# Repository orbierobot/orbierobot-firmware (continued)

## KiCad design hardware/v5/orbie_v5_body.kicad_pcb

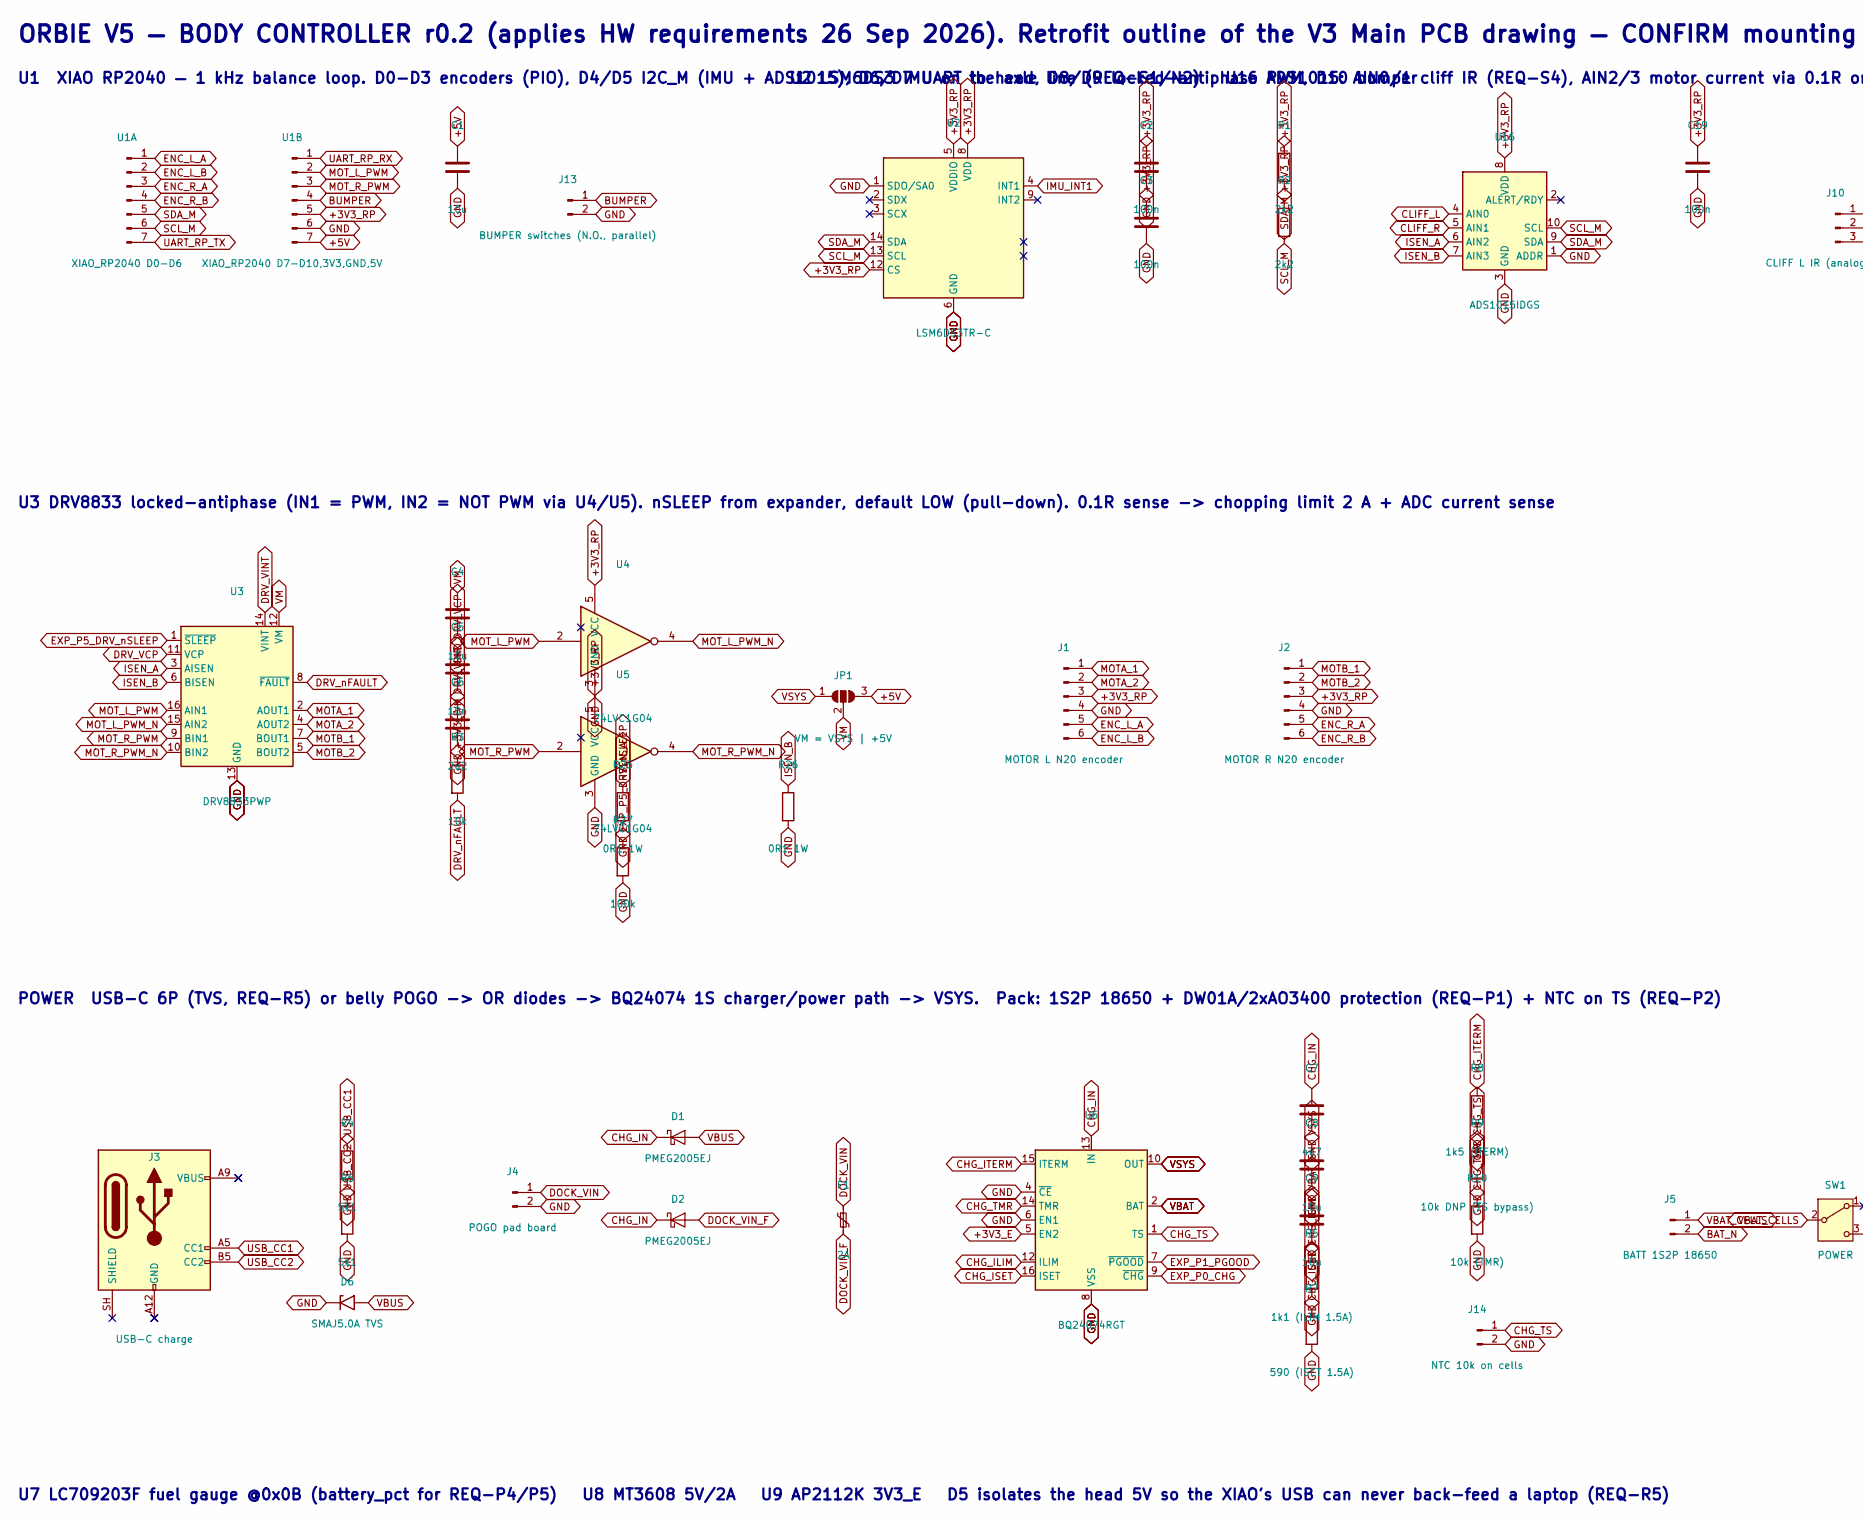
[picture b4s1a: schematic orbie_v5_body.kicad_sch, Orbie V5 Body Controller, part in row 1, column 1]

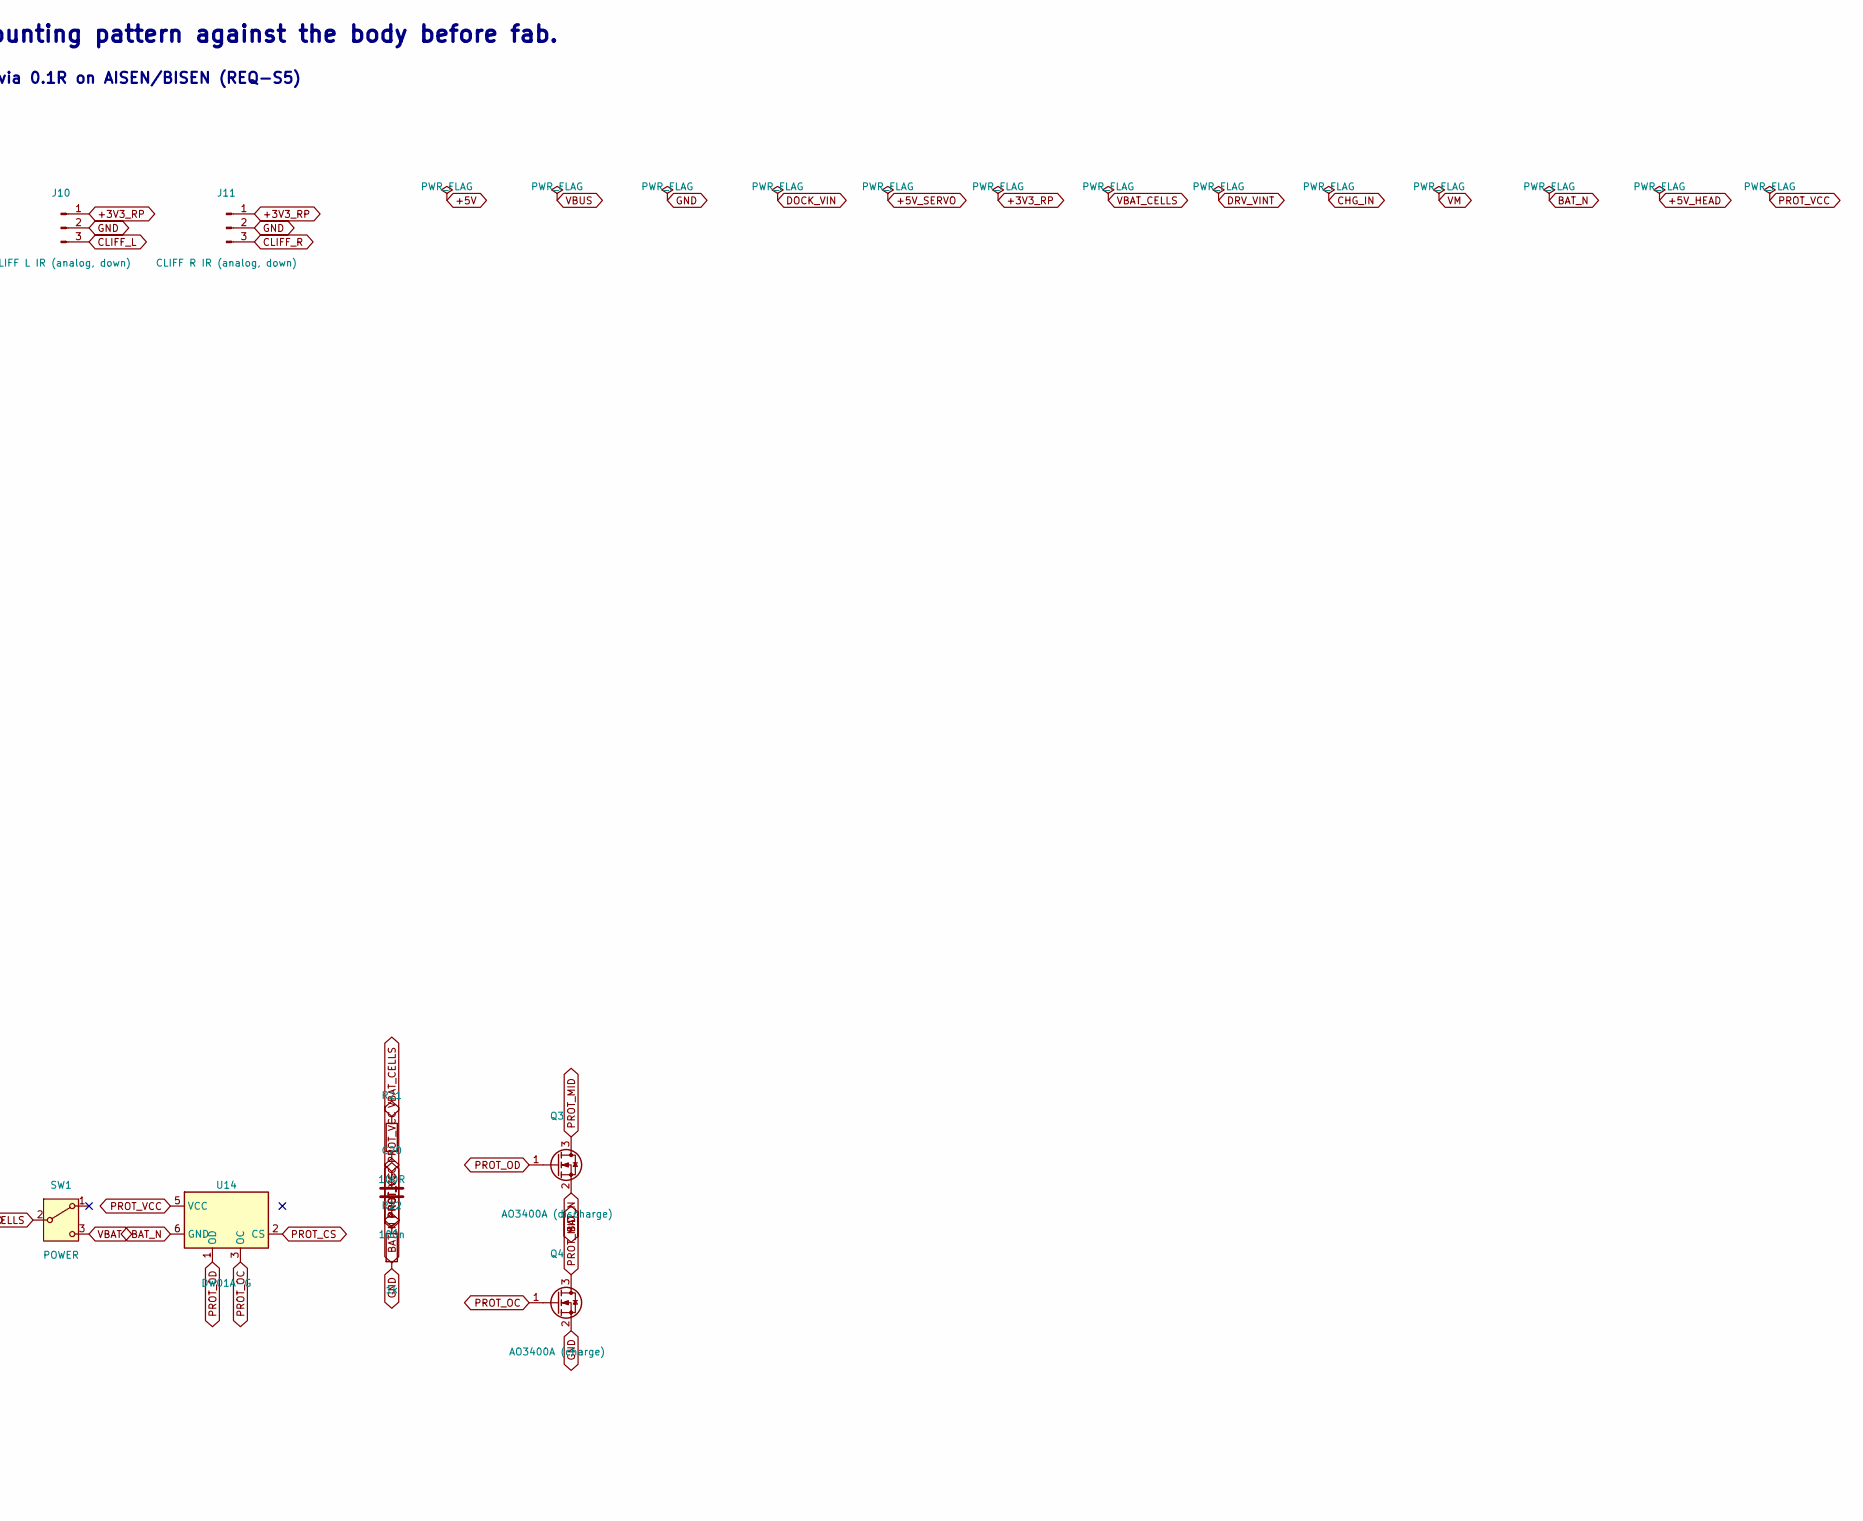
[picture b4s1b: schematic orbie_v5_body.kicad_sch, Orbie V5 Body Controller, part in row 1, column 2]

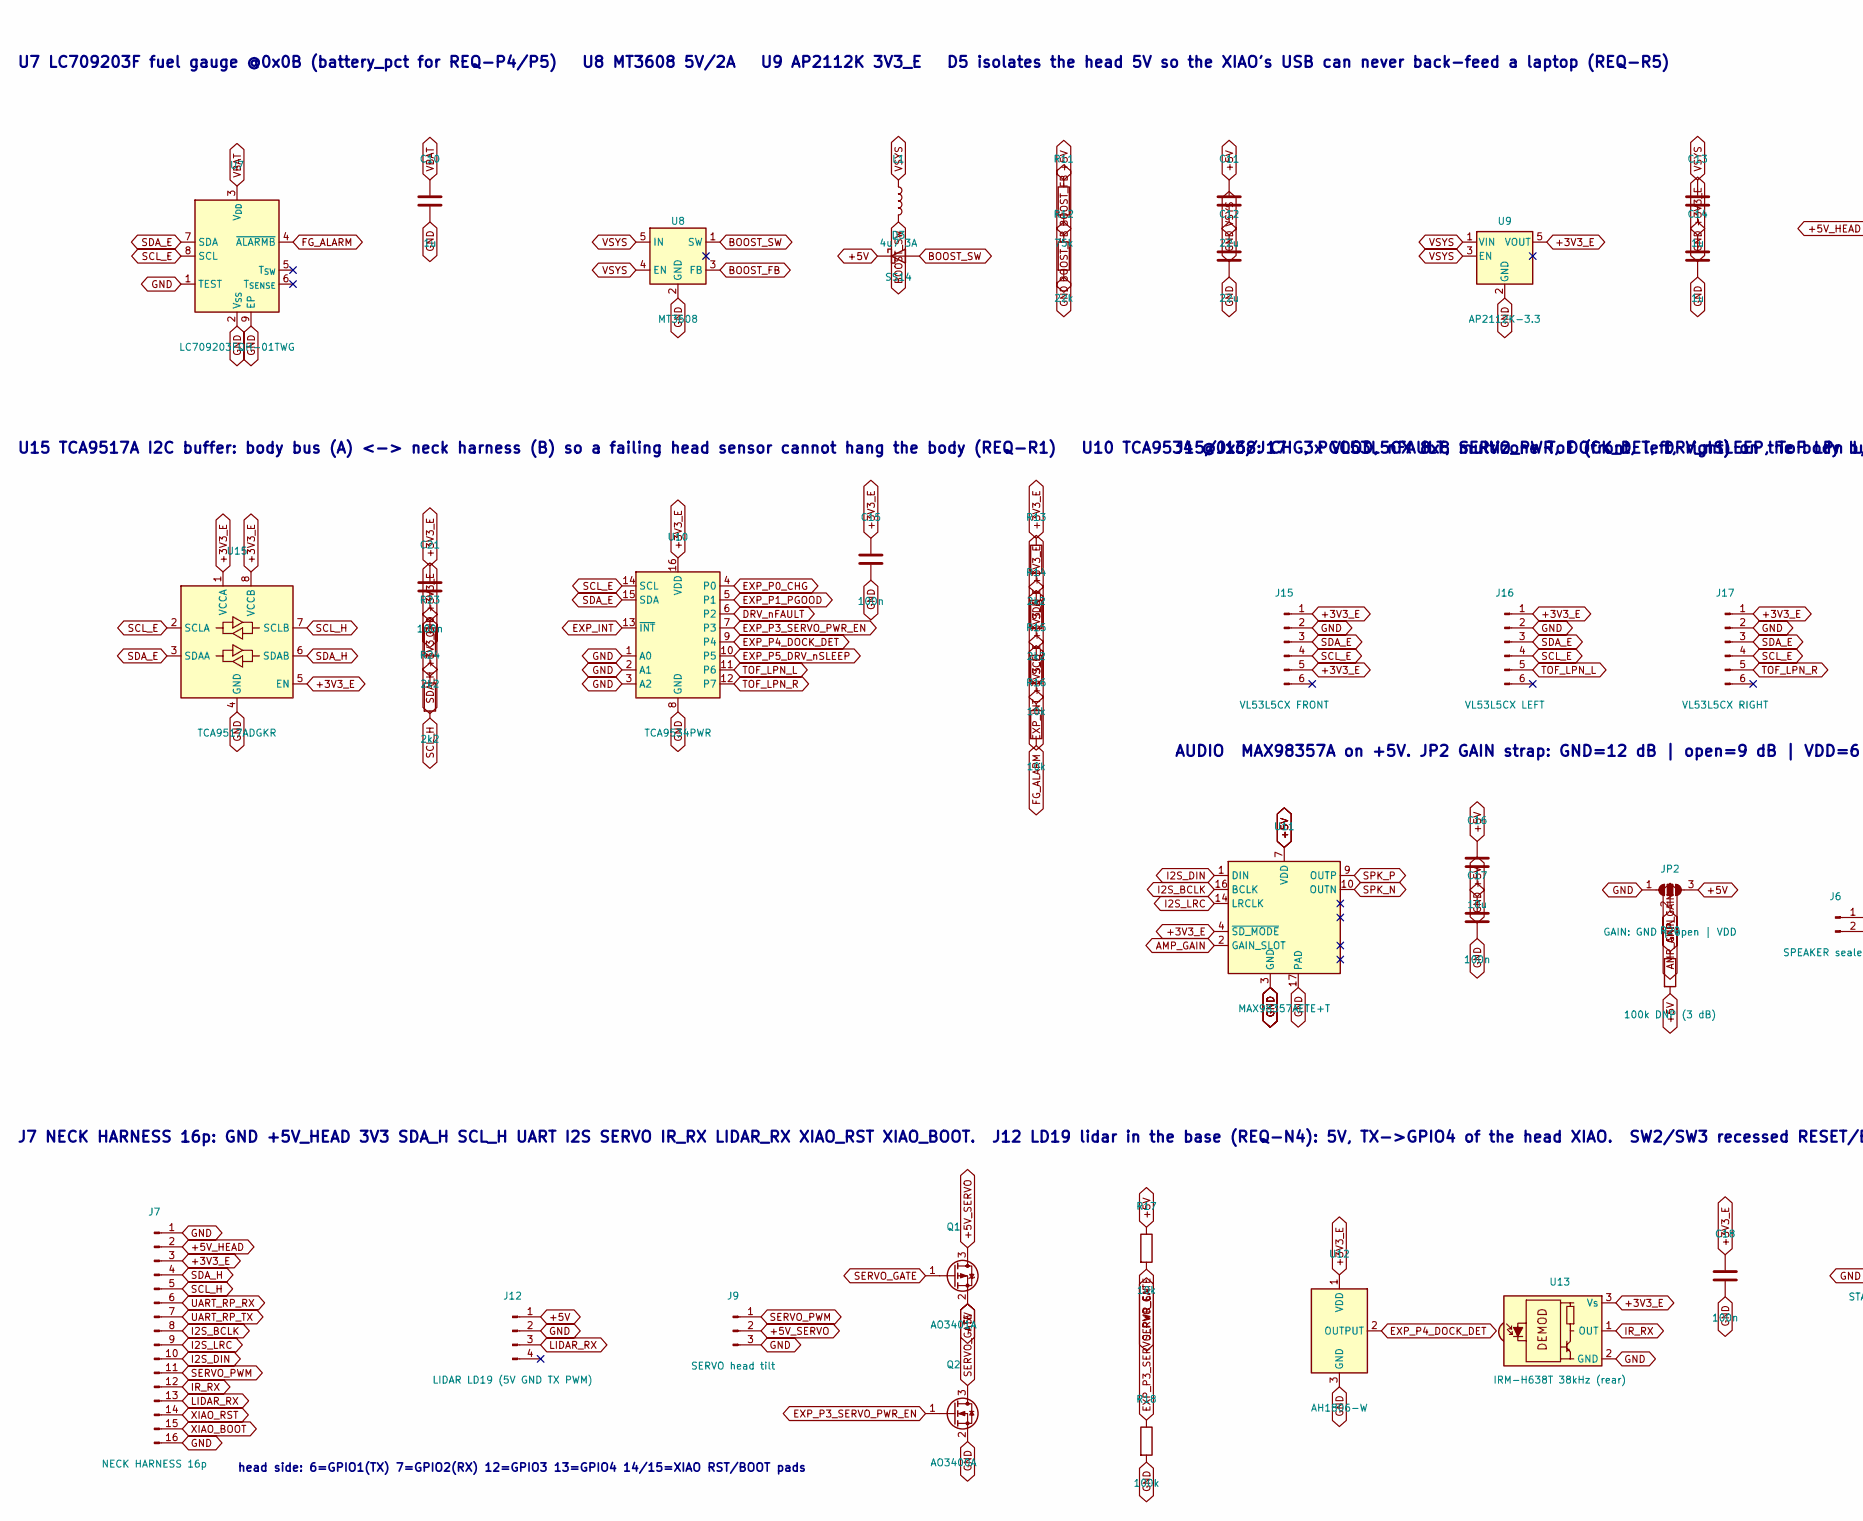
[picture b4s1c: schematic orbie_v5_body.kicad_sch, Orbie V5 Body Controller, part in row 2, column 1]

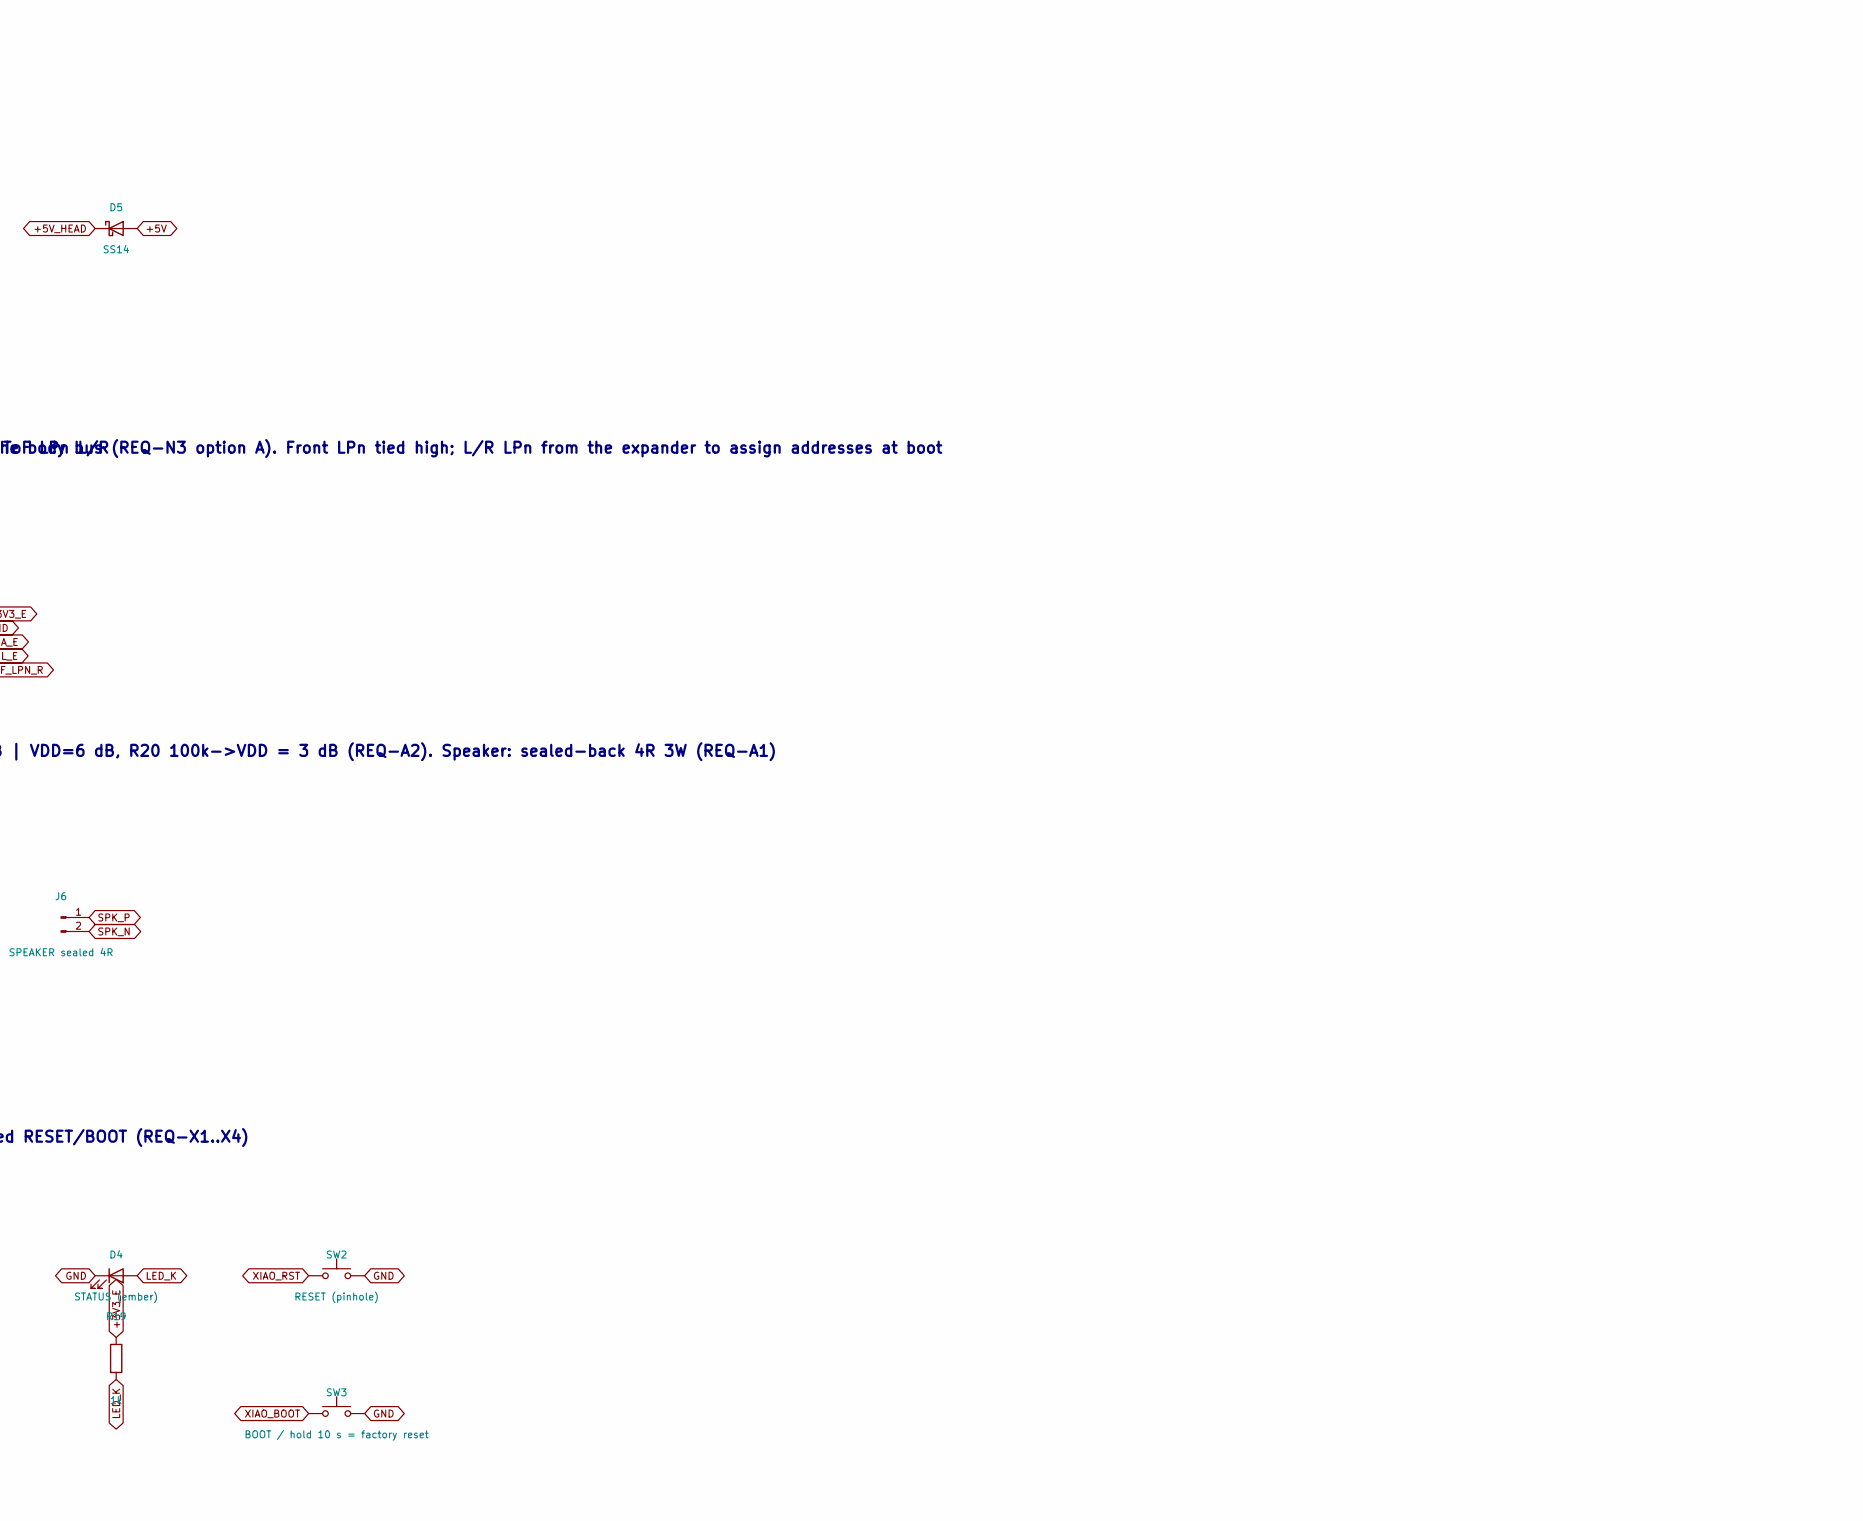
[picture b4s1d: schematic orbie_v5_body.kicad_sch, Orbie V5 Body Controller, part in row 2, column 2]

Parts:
C1, C4, C8, C9, C16: 10u; C_0805_2012Metric_Pad1.18x1.45mm_HandSolder
C2, C3, C15, C17, C18, C19, C20, C21: 100n; C_0603_1608Metric_Pad1.08x0.95mm_HandSolder
C5: 10n; C_0603_1608Metric_Pad1.08x0.95mm_HandSolder
C6: 2u2; C_0603_1608Metric_Pad1.08x0.95mm_HandSolder
C7: 4u7; C_0603_1608Metric_Pad1.08x0.95mm_HandSolder
C10, C13, C14: 1u; C_0603_1608Metric_Pad1.08x0.95mm_HandSolder
C11, C12: 22u; C_1210_3225Metric_Pad1.33x2.70mm_HandSolder
D1, D2: PMEG2005EJ; D_SOD-323F
D3, D5: SS14; D_SMA
D4: STATUS (ember); LED_0603_1608Metric
D6: SMAJ5.0A TVS; D_SMA
F1: 2A; Fuse_1206_3216Metric
J1: MOTOR L N20 encoder; JST_PH_B6B-PH-K_1x06_P2.00mm_Vertical
J2: MOTOR R N20 encoder; JST_PH_B6B-PH-K_1x06_P2.00mm_Vertical
J3: USB-C charge; USB_C_Receptacle_GCT_USB4125-xx-x_6P_TopMnt_Horizontal
J4: POGO pad board; JST_PH_B2B-PH-K_1x02_P2.00mm_Vertical
J5: BATT 1S2P 18650; JST_XH_B2B-XH-A_1x02_P2.50mm_Vertical
J6: SPEAKER sealed 4R; JST_PH_B2B-PH-K_1x02_P2.00mm_Vertical
J7: NECK HARNESS 16p; JST_PH_B16B-PH-K_1x16_P2.00mm_Vertical
J9: SERVO head tilt; JST_PH_B3B-PH-K_1x03_P2.00mm_Vertical
J10: CLIFF L IR (analog, down); JST_PH_B3B-PH-K_1x03_P2.00mm_Vertical
J11: CLIFF R IR (analog, down); JST_PH_B3B-PH-K_1x03_P2.00mm_Vertical
J12: LIDAR LD19 (5V GND TX PWM); JST_ZH_B4B-ZR_1x04_P1.50mm_Vertical
J13: BUMPER switches (N.O., parallel); JST_PH_B2B-PH-K_1x02_P2.00mm_Vertical
J14: NTC 10k on cells; JST_PH_B2B-PH-K_1x02_P2.00mm_Vertical
J15: VL53L5CX FRONT; JST_PH_B6B-PH-K_1x06_P2.00mm_Vertical
J16: VL53L5CX LEFT; JST_PH_B6B-PH-K_1x06_P2.00mm_Vertical
J17: VL53L5CX RIGHT; JST_PH_B6B-PH-K_1x06_P2.00mm_Vertical
JP1: VM = VSYS | +5V; SolderJumper-3_P1.3mm_Open_RoundedPad1.0x1.5mm
JP2: GAIN: GND | open | VDD; SolderJumper-3_P1.3mm_Open_RoundedPad1.0x1.5mm
L1: 4u7 3A; L_Taiyo-Yuden_NR-40xx
Q1: AO3401A; SOT-23_Handsoldering
Q2: AO3400A; SOT-23_Handsoldering
Q3: AO3400A (discharge); SOT-23_Handsoldering
Q4: AO3400A (charge); SOT-23_Handsoldering
R1, R2, R13, R14, R23, R24: 2k2; R_0603_1608Metric_Pad0.98x0.95mm_HandSolder
R3, R15, R16, R17: 10k; R_0603_1608Metric_Pad0.98x0.95mm_HandSolder
R4, R5: 5k1; R_0603_1608Metric_Pad0.98x0.95mm_HandSolder
R6: 1k1 (ILIM 1.5A); R_0603_1608Metric_Pad0.98x0.95mm_HandSolder
R7: 590 (ISET 1.5A); R_0603_1608Metric_Pad0.98x0.95mm_HandSolder
R8: 1k5 (ITERM); R_0603_1608Metric_Pad0.98x0.95mm_HandSolder
R9: 10k DNP (TS bypass); R_0603_1608Metric_Pad0.98x0.95mm_HandSolder
R10: 10k (TMR); R_0603_1608Metric_Pad0.98x0.95mm_HandSolder
R11: 75k; R_0603_1608Metric_Pad0.98x0.95mm_HandSolder
R12: 22k; R_0603_1608Metric_Pad0.98x0.95mm_HandSolder
R18, R27: 100k; R_0603_1608Metric_Pad0.98x0.95mm_HandSolder
R19, R22: 1k; R_0603_1608Metric_Pad0.98x0.95mm_HandSolder
R20: 100k DNP (3 dB); R_0603_1608Metric_Pad0.98x0.95mm_HandSolder
R21: 100R; R_0603_1608Metric_Pad0.98x0.95mm_HandSolder
R25, R26: 0R1 1W; R_1206_3216Metric
SW1: POWER; SW_SPDT_PCM12
SW2: RESET (pinhole); SW_Push_SPST_NO_Alps_SKRK
SW3: BOOT / hold 10 s = factory reset; SW_Push_SPST_NO_Alps_SKRK
U1A: XIAO_RP2040 D0-D6; XIAO_Castellated
U1B: XIAO_RP2040 D7-D10,3V3,GND,5V; XIAO_Castellated
U2: LSM6DS3TR-C; LGA-14_3x2.5mm_P0.5mm_LayoutBorder3x4y
U3: DRV8833PWP; HTSSOP-16-1EP_4.4x5mm_P0.65mm_EP3.4x5mm
U4, U5: 74LVC1G04; SOT-23-5_HandSoldering
U6: BQ24074RGT; VQFN-16-1EP_3x3mm_P0.5mm_EP1.68x1.68mm
U7: LC709203FQH-01TWG; WDFN-8-1EP_3x2mm_P0.5mm_EP1.3x1.4mm
U8: MT3608; SOT-23-6
U9: AP2112K-3.3; SOT-23-5_HandSoldering
U10: TCA9534PWR; TSSOP-16_4.4x5mm_P0.65mm
U11: MAX98357AETE+T; QFN-16-1EP_3x3mm_P0.5mm_EP1.75x1.75mm
U12: AH1806-W; SOT-23_Handsoldering
U13: IRM-H638T 38kHz (rear); Everlight_IRM-H6xxT
U14: DW01A-G; SOT-23-6_Handsoldering
U15: TCA9517ADGKR; MSOP-8_3x3mm_P0.65mm
U16: ADS1015IDGS; TSSOP-10_3x3mm_P0.5mm

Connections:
+3V3_E: C14.1, C15.1, C18.1, C21.1, J7.3, J15.1, J15.5, J16.1, J17.1, R3.1, R13.1, R14.1, R15.1, R16.1, R19.1, R23.1, R24.1, U6.5 (EN2), U9.5 (VOUT), U10.16 (VDD), U11.4 (~SD_MODE), U12.1 (VDD), U13.3 (Vs), U15.1 (VCCA), U15.5 (EN), U15.8 (VCCB)
+3V3_RP: C2.1, C3.1, C19.1, J1.3, J2.3, J10.1, J11.1, R1.1, R2.1, U1A.12, U1B.5, U2.5 (VDDIO), U2.8 (VDD), U2.12 (CS), U4.5 (VCC), U5.5 (VCC), U16.8 (VDD)
+5V: C1.1, C11.1, C16.1, C17.1, D3.1 (K), D5.2 (A), J12.1, JP1.3 (B), JP2.3 (B), Q1.2 (S), R11.1, R17.1, R20.2, U1A.14, U1B.7, U11.7 (VDD), U11.8 (VDD)
+5V_HEAD: D5.1 (K), J7.2
+5V_SERVO: J9.2, Q1.3 (D)
AMP_GAIN: JP2.2 (C), R20.1, U11.2 (GAIN_SLOT)
BAT_N: C20.2, J5.2, Q3.2 (S), U14.6 (GND)
BOOST_FB: R11.2, R12.1, U8.3 (FB)
BOOST_SW: D3.2 (A), L1.2, U8.1 (SW)
BUMPER: J13.1, U1A.11, U1B.4
CHG_ILIM: R6.1, U6.12 (ILIM)
CHG_IN: C7.1, D1.1 (K), D2.1 (K), U6.13 (IN)
CHG_ISET: R7.1, U6.16 (ISET)
CHG_ITERM: R8.1, U6.15 (ITERM)
CHG_TMR: R10.1, U6.14 (TMR)
CHG_TS: J14.1, R9.1, U6.1 (TS)
CLIFF_L: J10.3, U16.4 (AIN0)
CLIFF_R: J11.3, U16.5 (AIN1)
DOCK_VIN: F1.1, J4.1
DOCK_VIN_F: D2.2 (A), F1.2
DRV_VCP: C5.1, U3.11 (VCP)
DRV_VINT: C6.1, U3.14 (VINT)
DRV_nFAULT: R3.2, U3.8 (~FAULT), U10.6 (P2)
ENC_L_A: J1.5, U1A.1
ENC_L_B: J1.6, U1A.2
ENC_R_A: J2.5, U1A.3
ENC_R_B: J2.6, U1A.4
EXP_INT: R15.2, U10.13 (~INT)
EXP_P0_CHG: U6.9 (~CHG), U10.4 (P0)
EXP_P1_PGOOD: U6.7 (~PGOOD), U10.5 (P1)
EXP_P3_SERVO_PWR_EN: Q2.1 (G), R18.1, U10.7 (P3)
EXP_P4_DOCK_DET: U10.9 (P4), U12.2 (OUTPUT)
EXP_P5_DRV_nSLEEP: R27.1, U3.1 (~SLEEP), U10.10 (P5)
FG_ALARM: R16.2, U7.4 (~ALARMB)
GND: C1.2, C2.2, C3.2, C4.2, C6.2, C7.2, C8.2, C9.2, C10.2, C11.2, C12.2, C13.2, C14.2, C15.2, C16.2, C17.2, C18.2, C19.2, C21.2, D4.1 (K), D6.1 (A1), J1.4, J2.4, J4.2, J7.1, J7.16, J9.3, J10.2, J11.2, J12.2, J13.2, J14.2, J15.2, J16.2, J17.2, JP2.1 (A), Q2.2 (S), Q4.2 (S), R4.2, R5.2, R6.2, R7.2, R8.2, R9.2, R10.2, R12.2, R18.2, R22.2, R25.2, R26.2, R27.2, SW2.2, SW3.2, U1A.13, U1B.6, U2.1 (SDO/SA0), U2.6 (GND), U2.7 (GND), U3.13 (GND), U3.17 (GND), U4.3 (GND), U5.3 (GND), U6.4 (~CE), U6.6 (EN1), U6.8 (VSS), U6.17 (VSS), U7.1 (TEST), U7.2 (V_{SS}), U7.9 (EP), U8.2 (GND), U9.2 (GND), U10.1 (A0), U10.2 (A1), U10.3 (A2), U10.8 (GND), U11.3 (GND), U11.11 (GND), U11.15 (GND), U11.17 (PAD), U12.3 (GND), U13.2 (GND), U15.4 (GND), U16.1 (ADDR), U16.3 (GND)
I2S_BCLK: J7.8, U11.16 (BCLK)
I2S_DIN: J7.10, U11.1 (DIN)
I2S_LRC: J7.9, U11.14 (LRCLK)
IMU_INT1: U2.4 (INT1)
IR_RX: J7.12, U13.1 (OUT)
ISEN_A: R25.1, U3.3 (AISEN), U16.6 (AIN2)
ISEN_B: R26.1, U3.6 (BISEN), U16.7 (AIN3)
LED_K: D4.2 (A), R19.2
LIDAR_RX: J7.13, J12.3
MOTA_1: J1.1, U3.2 (AOUT1)
MOTA_2: J1.2, U3.4 (AOUT2)
MOTB_1: J2.1, U3.7 (BOUT1)
MOTB_2: J2.2, U3.5 (BOUT2)
MOT_L_PWM: U1A.9, U1B.2, U3.16 (AIN1), U4.2
MOT_L_PWM_N: U3.15 (AIN2), U4.4
MOT_R_PWM: U1A.10, U1B.3, U3.9 (BIN1), U5.2
MOT_R_PWM_N: U3.10 (BIN2), U5.4
PROT_CS: R22.1, U14.2 (CS)
PROT_MID: Q3.3 (D), Q4.3 (D)
PROT_OC: Q4.1 (G), U14.3 (OC)
PROT_OD: Q3.1 (G), U14.1 (OD)
PROT_VCC: C20.1, R21.2, U14.5 (VCC)
SCL_E: J15.4, J16.4, J17.4, R14.2, U7.8 (SCL), U10.14 (SCL), U15.2 (SCLA)
SCL_H: J7.5, R24.2, U15.7 (SCLB)
SCL_M: R2.2, U1A.6, U2.13 (SCL), U16.10 (SCL)
SDA_E: J15.3, J16.3, J17.3, R13.2, U7.7 (SDA), U10.15 (SDA), U15.3 (SDAA)
SDA_H: J7.4, R23.2, U15.6 (SDAB)
SDA_M: R1.2, U1A.5, U2.14 (SDA), U16.9 (SDA)
SERVO_GATE: Q1.1 (G), Q2.3 (D), R17.2
SERVO_PWM: J7.11, J9.1
SPK_N: J6.2, U11.10 (OUTN)
SPK_P: J6.1, U11.9 (OUTP)
TOF_LPN_L: J16.5, U10.11 (P6)
TOF_LPN_R: J17.5, U10.12 (P7)
UART_RP_RX: J7.6, U1A.8, U1B.1
UART_RP_TX: J7.7, U1A.7
USB_CC1: J3.A5 (CC1), R4.1
USB_CC2: J3.B5 (CC2), R5.1
VBAT: C9.1, C10.1, SW1.3 (C), U6.2 (BAT), U6.3 (BAT), U7.3 (V_{DD})
VBAT_CELLS: J5.1, R21.1, SW1.2 (B)
VBUS: D1.2 (A), D6.2 (A2)
VM: C4.1, C5.2, JP1.2 (C), U3.12 (VM)
VSYS: C8.1, C12.1, C13.1, JP1.1 (A), L1.1, U6.10 (OUT), U6.11 (OUT), U8.4 (EN), U8.5 (IN), U9.1 (VIN), U9.3 (EN)
XIAO_BOOT: J7.15, SW3.1
XIAO_RST: J7.14, SW2.1

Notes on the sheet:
ORBIE V5 — BODY CONTROLLER r0.2 (applies HW requirements 26 Sep 2026). Retrofit outline of the V3 Main PCB drawing — CONFIRM mounting pattern against the body before fab.
U1 XIAO RP2040 — 1 kHz balance loop. D0-D3 encoders (PIO), D4/D5 I2C_M (IMU + ADS1015), D6/D7 UART to head, D8/D9 locked-antiphase PWM, D10 bumper
U2 LSM6DS3 IMU on the axle line (REQ-S1/N2) U16 ADS1015: AIN0/1 cliff IR (REQ-S4), AIN2/3 motor current via 0.1R on AISEN/BISEN (REQ-S5)
U3 DRV8833 locked-antiphase (IN1 = PWM, IN2 = NOT PWM via U4/U5). nSLEEP from expander, default LOW (pull-down). 0.1R sense -> chopping limit 2 A + ADC current sense
POWER USB-C 6P (TVS, REQ-R5) or belly POGO -> OR diodes -> BQ24074 1S charger/power path -> VSYS. Pack: 1S2P 18650 + DW01A/2xAO3400 protection (REQ-P1) + NTC on TS (REQ-P2)
U7 LC709203F fuel gauge @0x0B (battery_pct for REQ-P4/P5) U8 MT3608 5V/2A U9 AP2112K 3V3_E D5 isolates the head 5V so the XIAO's USB can never back-feed a laptop (REQ-R5)
U15 TCA9517A I2C buffer: body bus (A) <-> neck harness (B) so a failing head sensor cannot hang the body (REQ-R1) U10 TCA9534 @0x38: CHG, PGOOD, nFAULT, SERVO_PWR, DOCK_DET, DRV_nSLEEP, ToF LPn L/R
J15/J16/J17 3x VL53L5CX 8x8 multizone ToF (front, left, right) on the body bus (REQ-N3 option A). Front LPn tied high; L/R LPn from the expander to assign addresses at boot
AUDIO MAX98357A on +5V. JP2 GAIN strap: GND=12 dB | open=9 dB | VDD=6 dB, R20 100k->VDD = 3 dB (REQ-A2). Speaker: sealed-back 4R 3W (REQ-A1)
J7 NECK HARNESS 16p: GND +5V_HEAD 3V3 SDA_H SCL_H UART I2S SERVO IR_RX LIDAR_RX XIAO_RST XIAO_BOOT. J12 LD19 lidar in the base (REQ-N4): 5V, TX->GPIO4 of the head XIAO. SW2/SW3 recessed RESET/BOOT (REQ-X1..X4)
head side: 6=GPIO1(TX) 7=GPIO2(RX) 12=GPIO3 13=GPIO4 14/15=XIAO RST/BOOT pads

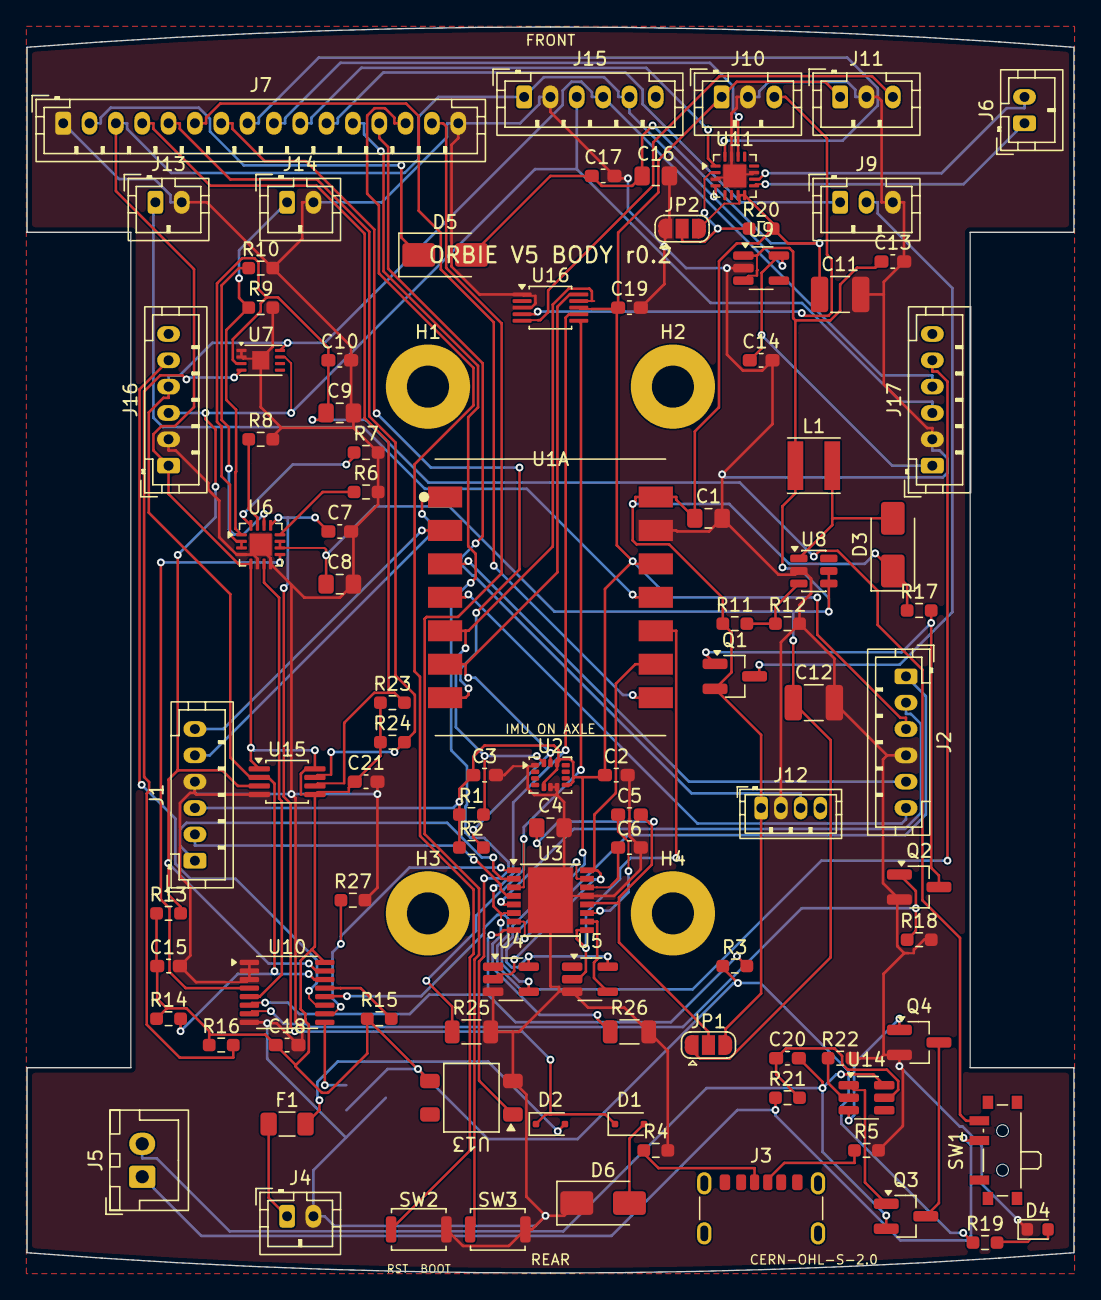
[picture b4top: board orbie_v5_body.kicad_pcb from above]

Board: 2 copper layers, 79.5 x 94.6 mm, 101 parts (1 on the bottom side), 79 nets.

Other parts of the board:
H1, H2, H3, H4: MountingHole_3.2mm_M3_Pad

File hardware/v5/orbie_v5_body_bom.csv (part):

Ref,Value,Symbol,Footprint,Side,Description
U1A,"XIAO_RP2040 D0-D6",Connector:Conn_01x07_Pin,orbie_v5:XIAO_Castellated,F,"XIAO RP2040 left row D0..D6"
U1B,"XIAO_RP2040 D7-D10,3V3,GND,5V",Connector:Conn_01x07_Pin,orbie_v5:XIAO_Castellated,F,"XIAO RP2040 right row (pins 8-14)"
C1,"10u",Device:C,Capacitor_SMD:C_0805_2012Metric_Pad1.18x1.45mm_HandSolder,F,"capacitor"
J13,"BUMPER switches (N.O., parallel)",Connector:Conn_01x02_Pin,Connector_JST:JST_PH_B2B-PH-K_1x02_P2.00mm_Vertical,F,"REQ-S5 contact detect"
U2,"LSM6DS3TR-C",Sensor_Motion:LSM6DS3,Package_LGA:LGA-14_3x2.5mm_P0.5mm_LayoutBorder3x4y,F,"6-axis IMU @0x6A"
C2,"100n",Device:C,Capacitor_SMD:C_0603_1608Metric_Pad1.08x0.95mm_HandSolder,F,"capacitor"
C3,"100n",Device:C,Capacitor_SMD:C_0603_1608Metric_Pad1.08x0.95mm_HandSolder,F,"capacitor"
R1,"2k2",Device:R,Resistor_SMD:R_0603_1608Metric_Pad0.98x0.95mm_HandSolder,F,"resistor"
R2,"2k2",Device:R,Resistor_SMD:R_0603_1608Metric_Pad0.98x0.95mm_HandSolder,F,"resistor"
U16,"ADS1015IDGS",Analog_ADC:ADS1015IDGS,Package_SO:TSSOP-10_3x3mm_P0.5mm,F,"4-ch 12-bit I2C ADC @0x48"
C19,"100n",Device:C,Capacitor_SMD:C_0603_1608Metric_Pad1.08x0.95mm_HandSolder,F,"capacitor"
J10,"CLIFF L IR (analog, down)",Connector:Conn_01x03_Pin,Connector_JST:JST_PH_B3B-PH-K_1x03_P2.00mm_Vertical,F,"downward IR reflective sensor, front edge"
J11,"CLIFF R IR (analog, down)",Connector:Conn_01x03_Pin,Connector_JST:JST_PH_B3B-PH-K_1x03_P2.00mm_Vertical,F,"downward IR reflective sensor, front edge"
U3,"DRV8833PWP",Driver_Motor:DRV8833PWP,Package_SO:HTSSOP-16-1EP_4.4x5mm_P0.65mm_EP3.4x5mm,F,"dual H-bridge"
C4,"10u",Device:C,Capacitor_SMD:C_0805_2012Metric_Pad1.18x1.45mm_HandSolder,F,"capacitor"
C5,"10n",Device:C,Capacitor_SMD:C_0603_1608Metric_Pad1.08x0.95mm_HandSolder,F,"capacitor"
C6,"2u2",Device:C,Capacitor_SMD:C_0603_1608Metric_Pad1.08x0.95mm_HandSolder,F,"capacitor"
R3,"10k",Device:R,Resistor_SMD:R_0603_1608Metric_Pad0.98x0.95mm_HandSolder,F,"resistor"
R25,"0R1 1W",Device:R,Resistor_SMD:R_1206_3216Metric,F,"resistor"
R26,"0R1 1W",Device:R,Resistor_SMD:R_1206_3216Metric,F,"resistor"
R27,"100k",Device:R,Resistor_SMD:R_0603_1608Metric_Pad0.98x0.95mm_HandSolder,F,"resistor"
U4,"74LVC1G04",74xGxx:74LVC1G04,Package_TO_SOT_SMD:SOT-23-5_HandSoldering,F,"inverter L"
U5,"74LVC1G04",74xGxx:74LVC1G04,Package_TO_SOT_SMD:SOT-23-5_HandSoldering,F,"inverter R"
JP1,"VM = VSYS | +5V",Jumper:SolderJumper_3_Open,Jumper:SolderJumper-3_P1.3mm_Open_RoundedPad1.0x1.5mm,F,"motor rail select"
J1,"MOTOR L N20 encoder",Connector:Conn_01x06_Pin,Connector_JST:JST_PH_B6B-PH-K_1x06_P2.00mm_Vertical,F,"GA12-N20 with magnetic encoder (REQ-N1)"
J2,"MOTOR R N20 encoder",Connector:Conn_01x06_Pin,Connector_JST:JST_PH_B6B-PH-K_1x06_P2.00mm_Vertical,F,"GA12-N20 with magnetic encoder (REQ-N1)"
J3,"USB-C charge",Connector:USB_C_Receptacle_PowerOnly_6P,Connector_USB:USB_C_Receptacle_GCT_USB4125-xx-x_6P_TopMnt_Horizontal,F,"USB-C 6P"
R4,"5k1",Device:R,Resistor_SMD:R_0603_1608Metric_Pad0.98x0.95mm_HandSolder,F,"resistor"
R5,"5k1",Device:R,Resistor_SMD:R_0603_1608Metric_Pad0.98x0.95mm_HandSolder,F,"resistor"
D6,"SMAJ5.0A TVS",Diode:SMAJ5.0A,Diode_SMD:D_SMA,F,"USB surge"
J4,"POGO pad board",Connector:Conn_01x02_Pin,Connector_JST:JST_PH_B2B-PH-K_1x02_P2.00mm_Vertical,F,"to belly pads"
D1,"PMEG2005EJ",Diode:PMEG2005EJ,Diode_SMD:D_SOD-323F,F,"OR-ing"
D2,"PMEG2005EJ",Diode:PMEG2005EJ,Diode_SMD:D_SOD-323F,F,"OR-ing"
F1,"2A",Device:Polyfuse_Small,Fuse:Fuse_1206_3216Metric,F,""
U6,"BQ24074RGT",Battery_Management:BQ24074RGT,Package_DFN_QFN:VQFN-16-1EP_3x3mm_P0.5mm_EP1.68x1.68mm,F,"1S charger + power path"
C7,"4u7",Device:C,Capacitor_SMD:C_0603_1608Metric_Pad1.08x0.95mm_HandSolder,F,"capacitor"
C8,"10u",Device:C,Capacitor_SMD:C_0805_2012Metric_Pad1.18x1.45mm_HandSolder,F,"capacitor"
C9,"10u",Device:C,Capacitor_SMD:C_0805_2012Metric_Pad1.18x1.45mm_HandSolder,F,"capacitor"
R6,"1k1 (ILIM 1.5A)",Device:R,Resistor_SMD:R_0603_1608Metric_Pad0.98x0.95mm_HandSolder,F,"resistor"
R7,"590 (ISET 1.5A)",Device:R,Resistor_SMD:R_0603_1608Metric_Pad0.98x0.95mm_HandSolder,F,"resistor"
R8,"1k5 (ITERM)",Device:R,Resistor_SMD:R_0603_1608Metric_Pad0.98x0.95mm_HandSolder,F,"resistor"
R9,"10k DNP (TS bypass)",Device:R,Resistor_SMD:R_0603_1608Metric_Pad0.98x0.95mm_HandSolder,F,"resistor"
R10,"10k (TMR)",Device:R,Resistor_SMD:R_0603_1608Metric_Pad0.98x0.95mm_HandSolder,F,"resistor"
J14,"NTC 10k on cells",Connector:Conn_01x02_Pin,Connector_JST:JST_PH_B2B-PH-K_1x02_P2.00mm_Vertical,F,"REQ-P2 charge temperature interlock"
J5,"BATT 1S2P 18650",Connector:Conn_01x02_Pin,Connector_JST:JST_XH_B2B-XH-A_1x02_P2.50mm_Vertical,F,"V3 pack (2 cells parallel)"
SW1,"POWER",Switch:SW_SPDT,Button_Switch_SMD:SW_SPDT_PCM12,F,"main power"
U14,"DW01A-G",Battery_Management:DW01A,Package_TO_SOT_SMD:SOT-23-6_Handsoldering,F,"1S protection"
R21,"100R",Device:R,Resistor_SMD:R_0603_1608Metric_Pad0.98x0.95mm_HandSolder,F,"resistor"
C20,"100n",Device:C,Capacitor_SMD:C_0603_1608Metric_Pad1.08x0.95mm_HandSolder,F,"capacitor"
R22,"1k",Device:R,Resistor_SMD:R_0603_1608Metric_Pad0.98x0.95mm_HandSolder,F,"resistor"
Q3,"AO3400A (discharge)",Transistor_FET:AO3400A,Package_TO_SOT_SMD:SOT-23_Handsoldering,F,"DW01 OD switch"
Q4,"AO3400A (charge)",Transistor_FET:AO3400A,Package_TO_SOT_SMD:SOT-23_Handsoldering,F,"DW01 OC switch"
U7,"LC709203FQH-01TWG",Battery_Management:LC709203FQH-01TWG,Package_DFN_QFN:WDFN-8-1EP_3x2mm_P0.5mm_EP1.3x1.4mm,F,"fuel gauge"
C10,"1u",Device:C,Capacitor_SMD:C_0603_1608Metric_Pad1.08x0.95mm_HandSolder,F,"capacitor"
U8,"MT3608",Regulator_Switching:MT3608,Package_TO_SOT_SMD:SOT-23-6,F,"boost"
L1,"4u7 3A",Device:L,Inductor_SMD:L_Taiyo-Yuden_NR-40xx,F,""
D3,"SS14",Diode:SS14,Diode_SMD:D_SMA,F,""
R11,"75k",Device:R,Resistor_SMD:R_0603_1608Metric_Pad0.98x0.95mm_HandSolder,F,"resistor"
R12,"22k",Device:R,Resistor_SMD:R_0603_1608Metric_Pad0.98x0.95mm_HandSolder,F,"resistor"
C11,"22u",Device:C,Capacitor_SMD:C_1210_3225Metric_Pad1.33x2.70mm_HandSolder,F,"capacitor"
C12,"22u",Device:C,Capacitor_SMD:C_1210_3225Metric_Pad1.33x2.70mm_HandSolder,F,"capacitor"
U9,"AP2112K-3.3",Regulator_Linear:AP2112K-3.3,Package_TO_SOT_SMD:SOT-23-5_HandSoldering,F,"3.3V LDO (board rail)"
C13,"1u",Device:C,Capacitor_SMD:C_0603_1608Metric_Pad1.08x0.95mm_HandSolder,F,"capacitor"
C14,"1u",Device:C,Capacitor_SMD:C_0603_1608Metric_Pad1.08x0.95mm_HandSolder,F,"capacitor"
D5,"SS14",Diode:SS14,Diode_SMD:D_SMA,F,"head 5V isolation"
U15,"TCA9517ADGKR",Logic_LevelTranslator:TCA9517ADGK,Package_SO:MSOP-8_3x3mm_P0.65mm,F,"I2C buffer"
C21,"100n",Device:C,Capacitor_SMD:C_0603_1608Metric_Pad1.08x0.95mm_HandSolder,F,"capacitor"
R23,"2k2",Device:R,Resistor_SMD:R_0603_1608Metric_Pad0.98x0.95mm_HandSolder,F,"resistor"
R24,"2k2",Device:R,Resistor_SMD:R_0603_1608Metric_Pad0.98x0.95mm_HandSolder,F,"resistor"
U10,"TCA9534PWR",Interface_Expansion:TCA9534,Package_SO:TSSOP-16_4.4x5mm_P0.65mm,F,"I/O expander"
C15,"100n",Device:C,Capacitor_SMD:C_0603_1608Metric_Pad1.08x0.95mm_HandSolder,F,"capacitor"
R13,"2k2",Device:R,Resistor_SMD:R_0603_1608Metric_Pad0.98x0.95mm_HandSolder,F,"resistor"
R14,"2k2",Device:R,Resistor_SMD:R_0603_1608Metric_Pad0.98x0.95mm_HandSolder,F,"resistor"
R15,"10k",Device:R,Resistor_SMD:R_0603_1608Metric_Pad0.98x0.95mm_HandSolder,F,"resistor"
R16,"10k",Device:R,Resistor_SMD:R_0603_1608Metric_Pad0.98x0.95mm_HandSolder,F,"resistor"
J15,"VL53L5CX FRONT",Connector:Conn_01x06_Pin,Connector_JST:JST_PH_B6B-PH-K_1x06_P2.00mm_Vertical,F,"8x8 ToF module"
J16,"VL53L5CX LEFT",Connector:Conn_01x06_Pin,Connector_JST:JST_PH_B6B-PH-K_1x06_P2.00mm_Vertical,F,"8x8 ToF module"
J17,"VL53L5CX RIGHT",Connector:Conn_01x06_Pin,Connector_JST:JST_PH_B6B-PH-K_1x06_P2.00mm_Vertical,F,"8x8 ToF module"
U11,"MAX98357AETE+T",Audio:MAX98357A,Package_DFN_QFN:QFN-16-1EP_3x3mm_P0.5mm_EP1.75x1.75mm,F,"I2S class-D"
C16,"10u",Device:C,Capacitor_SMD:C_0805_2012Metric_Pad1.18x1.45mm_HandSolder,F,"capacitor"
C17,"100n",Device:C,Capacitor_SMD:C_0603_1608Metric_Pad1.08x0.95mm_HandSolder,F,"capacitor"
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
